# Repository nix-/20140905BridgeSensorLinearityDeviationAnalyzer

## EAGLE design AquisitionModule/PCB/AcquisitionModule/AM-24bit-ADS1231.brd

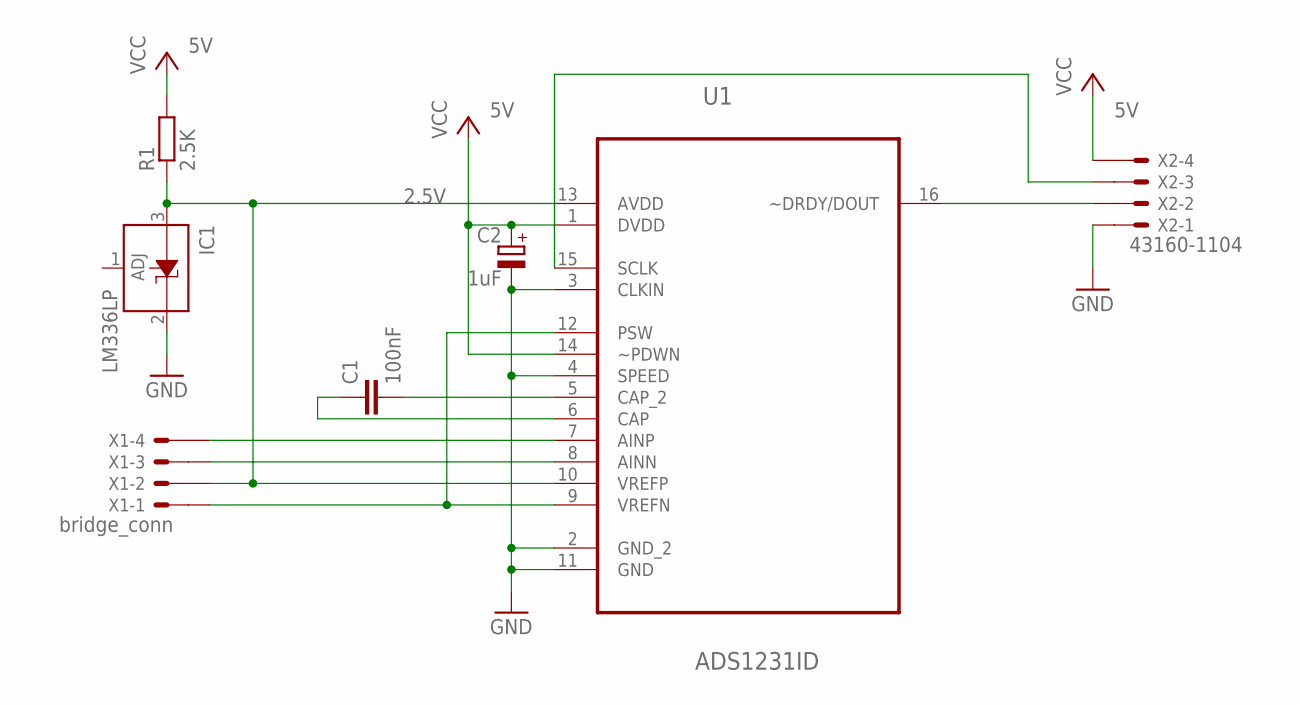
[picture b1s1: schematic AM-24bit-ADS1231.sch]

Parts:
C1: 100nF; C1206K
C2: 1uF; 153CLV-0505
IC1: LM336LP; TO92
R1: 2.5K; R3225W
U1: ADS1231ID; SOIC127P600X175-16N
X1: bridge_conn; 43160-XX04
X2: 43160-1104; 43160-XX04

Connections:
2.5V: IC1.3 (A), R1.1, U1.10 (VREFP), U1.13 (AVDD), X1.2@1
5V: C2.+, R1.2, U1.1 (DVDD), U1.14 (~PDWN), X2.4@1
GND: C2.-, IC1.2 (C), U1.2 (GND_2), U1.3 (CLKIN), U1.4 (SPEED), U1.11 (GND), X2.1@1
unnamed: C1.2, U1.5 (CAP_2)
unnamed: C1.1, U1.6 (CAP)
unnamed: U1.9 (VREFN), U1.12 (PSW), X1.1@1
unnamed: U1.7 (AINP), X1.4@1
unnamed: U1.8 (AINN), X1.3@1
unnamed: U1.15 (SCLK), X2.3@1
unnamed: U1.16 (~DRDY/DOUT), X2.2@1

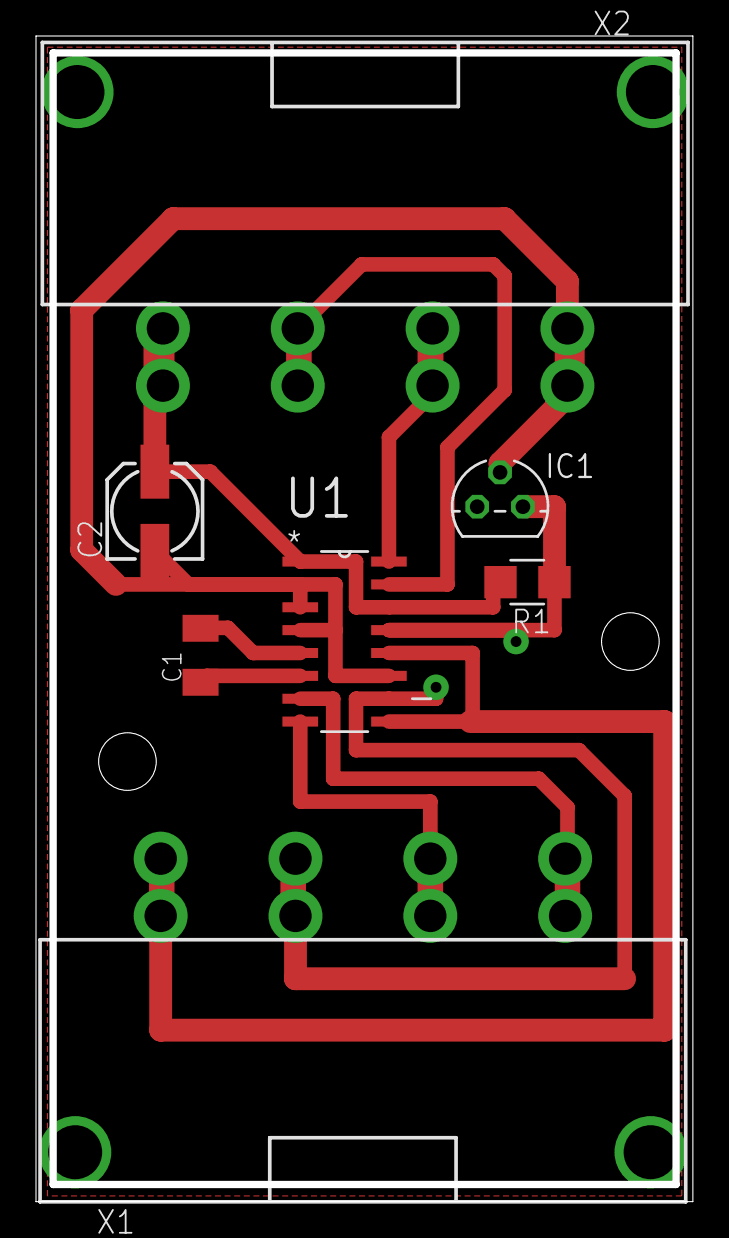
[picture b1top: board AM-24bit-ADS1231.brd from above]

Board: 2 copper layers, 36.1 x 64.4 mm, 7 parts (0 on the bottom side), 10 nets.

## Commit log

2014-09-05 Reorganizing the folder structure and deleted extra files
2014-09-05 Reorganization of the files in the project
2014-09-05 Changed comment in to the ReadMe.txt file
2014-09-05 Added ADC library in to the project
2014-09-05 Added - circuit document, components (Acquisition Module)
2014-09-05 Wiring components in Acquisition Module schematic
2014-09-16 Added reference voltage (2.5V) in the circuit
2014-09-16 Added file for PCB and wiring the components
2014-09-17 Added Eagle CAM Job file (saved settings for CAM)
2014-09-17 Added routes on PCB between Molex connector via and thickening the existing one..
2014-09-18 Added ADS1231 library, and porting interface ports. P0.8 - CLK P0.9 - DATA
2014-09-18 Solved bug related to external ADC CLK
2014-10-08 added libraries for external peripherals I2C port expander and LCD display
